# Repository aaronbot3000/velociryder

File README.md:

Velociryder Code
================

This is the software for the Velociryder, a self balancing two wheeled 
skateboard, started as a side project and was then entered in Georgia Tech's
2011 InVenture Prize. We made it all the way to the finals!

Features
--------

The code has the following features:
* PD control (no integral, wasn't necessary)
* Automatic startup via killswitch and level detection
* Support for foot pedal steering, just as in the Velociryder
* Use of accelerometer and gyroscope to obtain board level
* Moving average and complementary filters for the sensors

It works alright. 

Usage
-----
Things you will probably need to tweak:
### In velociryder.pde
* Turning constants

### In sensors.pde
* GYROTORAD4, GYROTORAD, ACCLTORAD: These convert the sensor's ADC units to 
	radians
* ACCL_CENTER: This defines the center balance point of the board
* sensor defines: The pins the sensors are on
* OHSHITSWITCH: killswitch pin

### In motors.pde
* However you control your motors

This is Arduino source code. So put it in a directory called velociryder in 
your sketchbook, fiddle, program, and go!

Implementations
---------------
* Version 1 of the Velociryder, back when it was called the Glide Board
http://www.youtube.com/watch?v=xvfUIxusPZw

* Version 2, built in aluminum and eliminated hand controller
http://www.gpb.org/inventure/velociryder

License
-------
This code is released under the MIT License. If you do use it, send me a 
message, I want to see it!

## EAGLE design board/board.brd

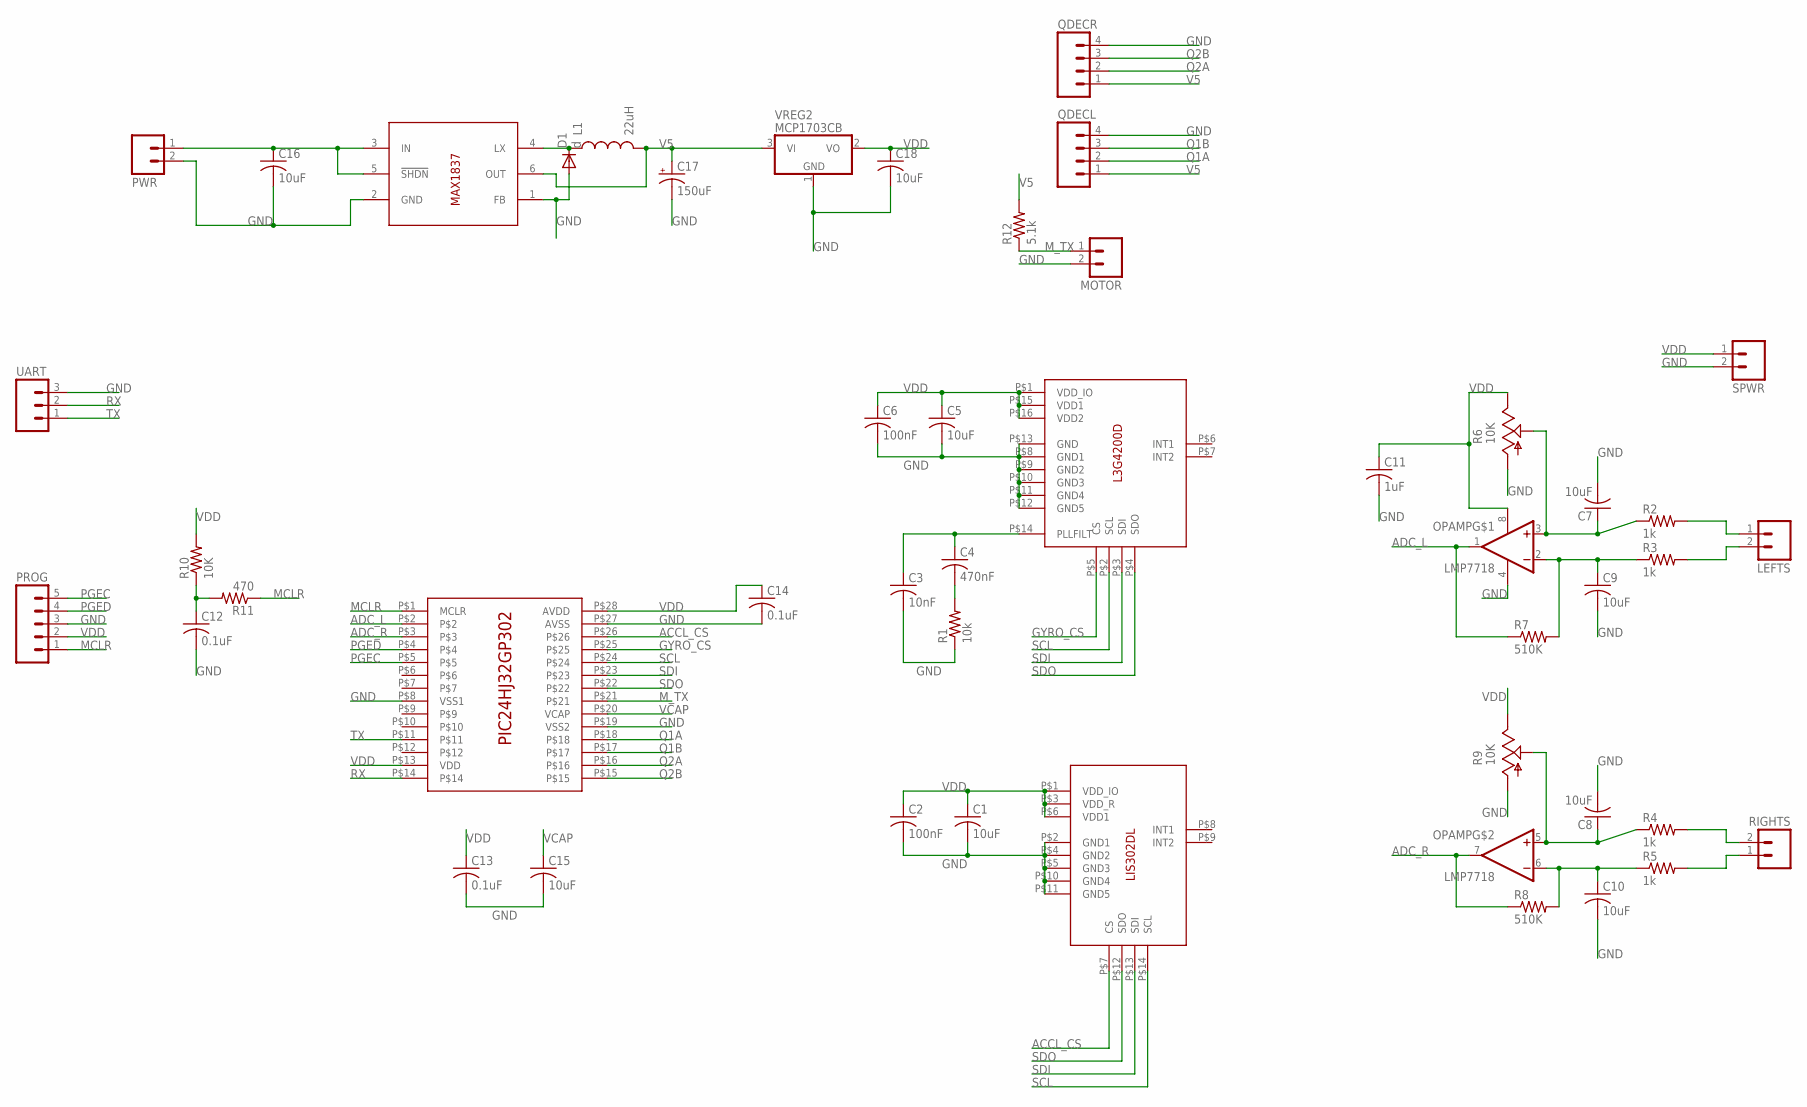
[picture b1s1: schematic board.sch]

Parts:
C1, C5, C15, C18: 10uF; C0805
C2, C6: 100nF; C0805
C3: 10nF; C0805
C4: 470nF; C0805
C7, C8, C9, C10, C16: 10uF; C1206
C11: 1uF; C0805
C12, C13, C14: 0.1uF; C0805
C17: 150uF; CT3528
D1: d; SOD-323
L1: 22uH; 1007
LEFTS: MOLEX-1X2
MOTOR: MOLEX-1X2
OPAMP: LMP7718; SO08
PROG: 1X05
PWR: MOLEX-1X2
QDECL: MOLEX-1X4
QDECR: MOLEX-1X4
R1: 10k; R0805
R2, R3, R4, R5: 1k; R1206
R6, R9: 10K; RJ6S
R7, R8: 510K; R0805
R10: 10K; R0805
R11: 470; R0805
R12: 5.1k; R0805
RIGHTS: MOLEX-1X2
SPWR: MOLEX-1X2
U$1: PIC24HJ32GP302; SOIC-28
U$2: L3G4200D; LGA-16
U$3: LIS302DL; LGA-14
UART: M03PTH; 1X03
VREG1: MAX1837; SOT23-6L
VREG2: MCP1703CB; SOT23

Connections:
ACCL_CS: U$1.P$26, U$3.P$7 (CS)
ADC_L: OPAMP.1 (OUT), R7.1, U$1.P$2
ADC_R: OPAMP.7 (OUT), R8.1, U$1.P$3
GND: C1.2, C2.2, C3.2, C5.2, C6.2, C7.2, C8.2, C9.2, C10.2, C11.2, C12.2, C13.2, C14.2, C15.2, C16.2, C17.-, C18.2, D1.2 (A), MOTOR.2, OPAMP.4 (V-), PROG.3, PWR.2, QDECL.4, QDECR.4, R1.1, R6.A, R9.A, SPWR.2, U$1.P$8 (VSS1), U$1.P$19 (VSS2), U$1.P$27 (AVSS), U$2.P$8 (GND1), U$2.P$9 (GND2), U$2.P$10 (GND3), U$2.P$11 (GND4), U$2.P$12 (GND5), U$2.P$13 (GND), U$3.P$2 (GND1), U$3.P$4 (GND2), U$3.P$5 (GND3), U$3.P$10 (GND4), U$3.P$11 (GND5), UART.3, VREG1.1 (FB), VREG1.2 (GND), VREG2.1 (GND)
GYRO_CS: U$1.P$25, U$2.P$5 (CS)
MCLR: PROG.1, R11.1, U$1.P$1 (MCLR)
M_TX: MOTOR.1, R12.1, U$1.P$21
unnamed: C16.1, PWR.1, VREG1.3 (IN), VREG1.5 (!SHDN)
unnamed: R4.2, RIGHTS.2
unnamed: C3.1, C4.1, U$2.P$14 (PLLFILT)
unnamed: C4.2, R1.2
unnamed: C7.1, OPAMP.3 (+IN), R2.1, R6.S
unnamed: C9.1, OPAMP.2 (-IN), R3.1, R7.2
unnamed: C10.1, OPAMP.6 (-IN), R5.1, R8.2
unnamed: LEFTS.1, R2.2
unnamed: LEFTS.2, R3.2
unnamed: R5.2, RIGHTS.1
unnamed: C8.1, OPAMP.5 (+IN), R4.1, R9.S
unnamed: D1.1 (C), L1.1, VREG1.4 (LX)
unnamed: C12.1, R10.1, R11.2
PGEC: PROG.5, U$1.P$5
PGED: PROG.4, U$1.P$4
Q1A: QDECL.2, U$1.P$18
Q1B: QDECL.3, U$1.P$17
Q2A: QDECR.2, U$1.P$16
Q2B: QDECR.3, U$1.P$15
RX: U$1.P$14, UART.2
SCL: U$1.P$24, U$2.P$2 (SCL), U$3.P$14 (SCL)
SDI: U$1.P$23, U$2.P$3 (SDI), U$3.P$13 (SDI)
SDO: U$1.P$22, U$2.P$4 (SDO), U$3.P$12 (SDO)
TX: U$1.P$11, UART.1
V5: C17.+, L1.2, QDECL.1, QDECR.1, R12.2, VREG1.6 (OUT), VREG2.3 (VI)
VCAP: C15.1, U$1.P$20 (VCAP)
VDD: C1.1, C2.1, C5.1, C6.1, C11.1, C13.1, C14.1, C18.1, OPAMP.8 (V+), PROG.2, R6.E, R9.E, R10.2, SPWR.1, U$1.P$13 (VDD), U$1.P$28 (AVDD), U$2.P$1 (VDD_IO), U$2.P$15 (VDD1), U$2.P$16 (VDD2), U$3.P$1 (VDD_IO), U$3.P$3 (VDD_R), U$3.P$6 (VDD1), VREG2.2 (VO)

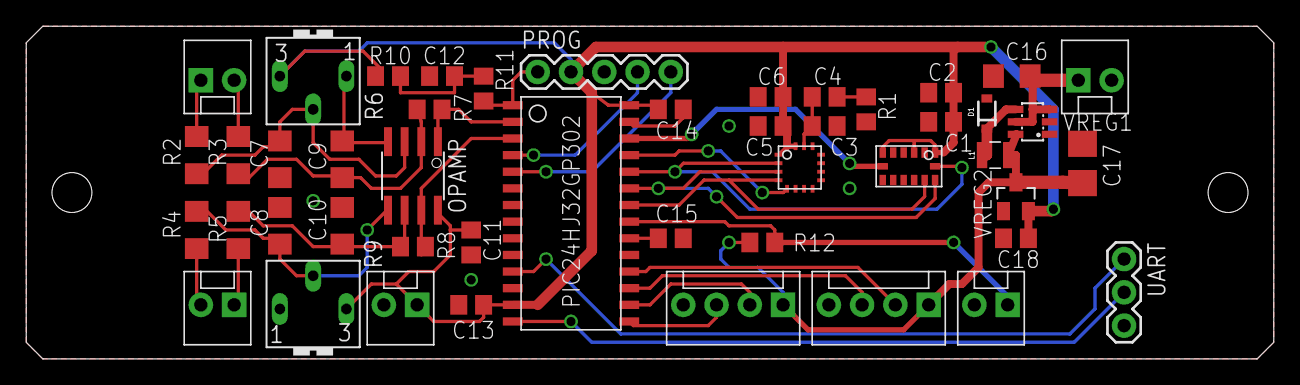
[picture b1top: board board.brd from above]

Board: 2 copper layers, 95.2 x 25.4 mm, 47 parts (0 on the bottom side), 34 nets.

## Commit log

2010-12-11 Add motors.pde, made progress
2010-12-11 more progress
2010-12-11 Woo it kinda works!
2010-12-11 Going to try something new and novel
2010-12-11 Change the PID controls to the previous gimped version
2010-12-12 Less instability! Can recover from minor disturbances
2010-12-12 Got a pretty good thing going
2011-01-12 Inverted D term, see what's up with that
2011-01-17 Add steering
2011-01-17 Twiddle constants
2011-01-18 Fix complementary filter and YGYRO selection
2011-01-18 Fiddle with variables
2011-01-18 Change integral term
2011-01-18 Fix the things the merge broken
2011-02-16 Right before modifying a lot for protov2
2011-02-16 Working ok, with these constants
2011-02-16 Fix steering
2011-02-18 More variable tweaking
2011-02-19 Start kalman filter implmentation
2011-02-19 clean variables
2011-02-19 more cleaning up variables
2011-02-19 Fix all the damn compile errors
2011-02-19 kalman porting complete, testing remains
2011-02-20 Completed implementation. Response seems laggy
2011-02-24 Experiment with different Q values
2011-03-03 clean up unused stuff, add z accl reading
2011-03-03 Switch to radians, get rid of this division by 7 nonsense
2011-03-05 lolololol gyro to rads was incorrect
2011-03-05 A bit of code cleanup
2011-03-05 Woo working now
2011-03-05 Implemented
2011-03-05 Switch back to using first order approximation for accl angle
2011-03-05 Works pretty well
2011-03-13 Switch to a moving average filter, and it works better
2011-03-13 Rename main program to something sensible
2011-03-13 Add license and readme
2011-03-13 Add license to file headers
    Also, renamed a variable in sensors
2011-03-13 Added to readme
2011-03-13 Add readme
2011-03-13 Add to readme
2012-01-23 Add gitignore file
2012-01-23 Add solidworks models for v4
2012-01-23 Add EAGLE CAD files
2012-01-23 move legacy arduino code to its own folder
2012-01-23 Continue work on the model
2012-01-24 Rename wheel gear, make wheel-gear assembly
2012-01-24 Add rough axle
2012-01-24 Rename gear-motor
2012-01-24 Add complete assembly and delete old gear-motor
2012-01-24 Something?
2012-01-24 New gears for new gear ratio and better sizes
2012-01-24 Fixing case sensitivity on Windows
2012-01-24 Final fix of Windows case insensitivity
2012-01-24 Make the bore not stupid
2012-01-24 Make the frame its own assembly
2012-01-24 Continue work
2012-02-11 Lots of work on the solidworks models. Mostly finished
2012-02-11 Update gitignore
2012-02-11 Add controller board files
2012-02-11 Update gitignore once more
2012-03-02 Finalize board.
2012-03-02 Super solidworks update.
2012-03-02 Fix axle length
2012-03-02 Add the rest of the strain gauges
2012-03-02 I think I did something
2012-03-02 Rename machining prep file
2012-03-13 laskjflasjdflaskjfdlasjdflsj

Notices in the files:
parts and their libraries:
SparkFun: Licensing: CC v3.0 Share-Alike You are welcome to use this library for commercial purposes.
